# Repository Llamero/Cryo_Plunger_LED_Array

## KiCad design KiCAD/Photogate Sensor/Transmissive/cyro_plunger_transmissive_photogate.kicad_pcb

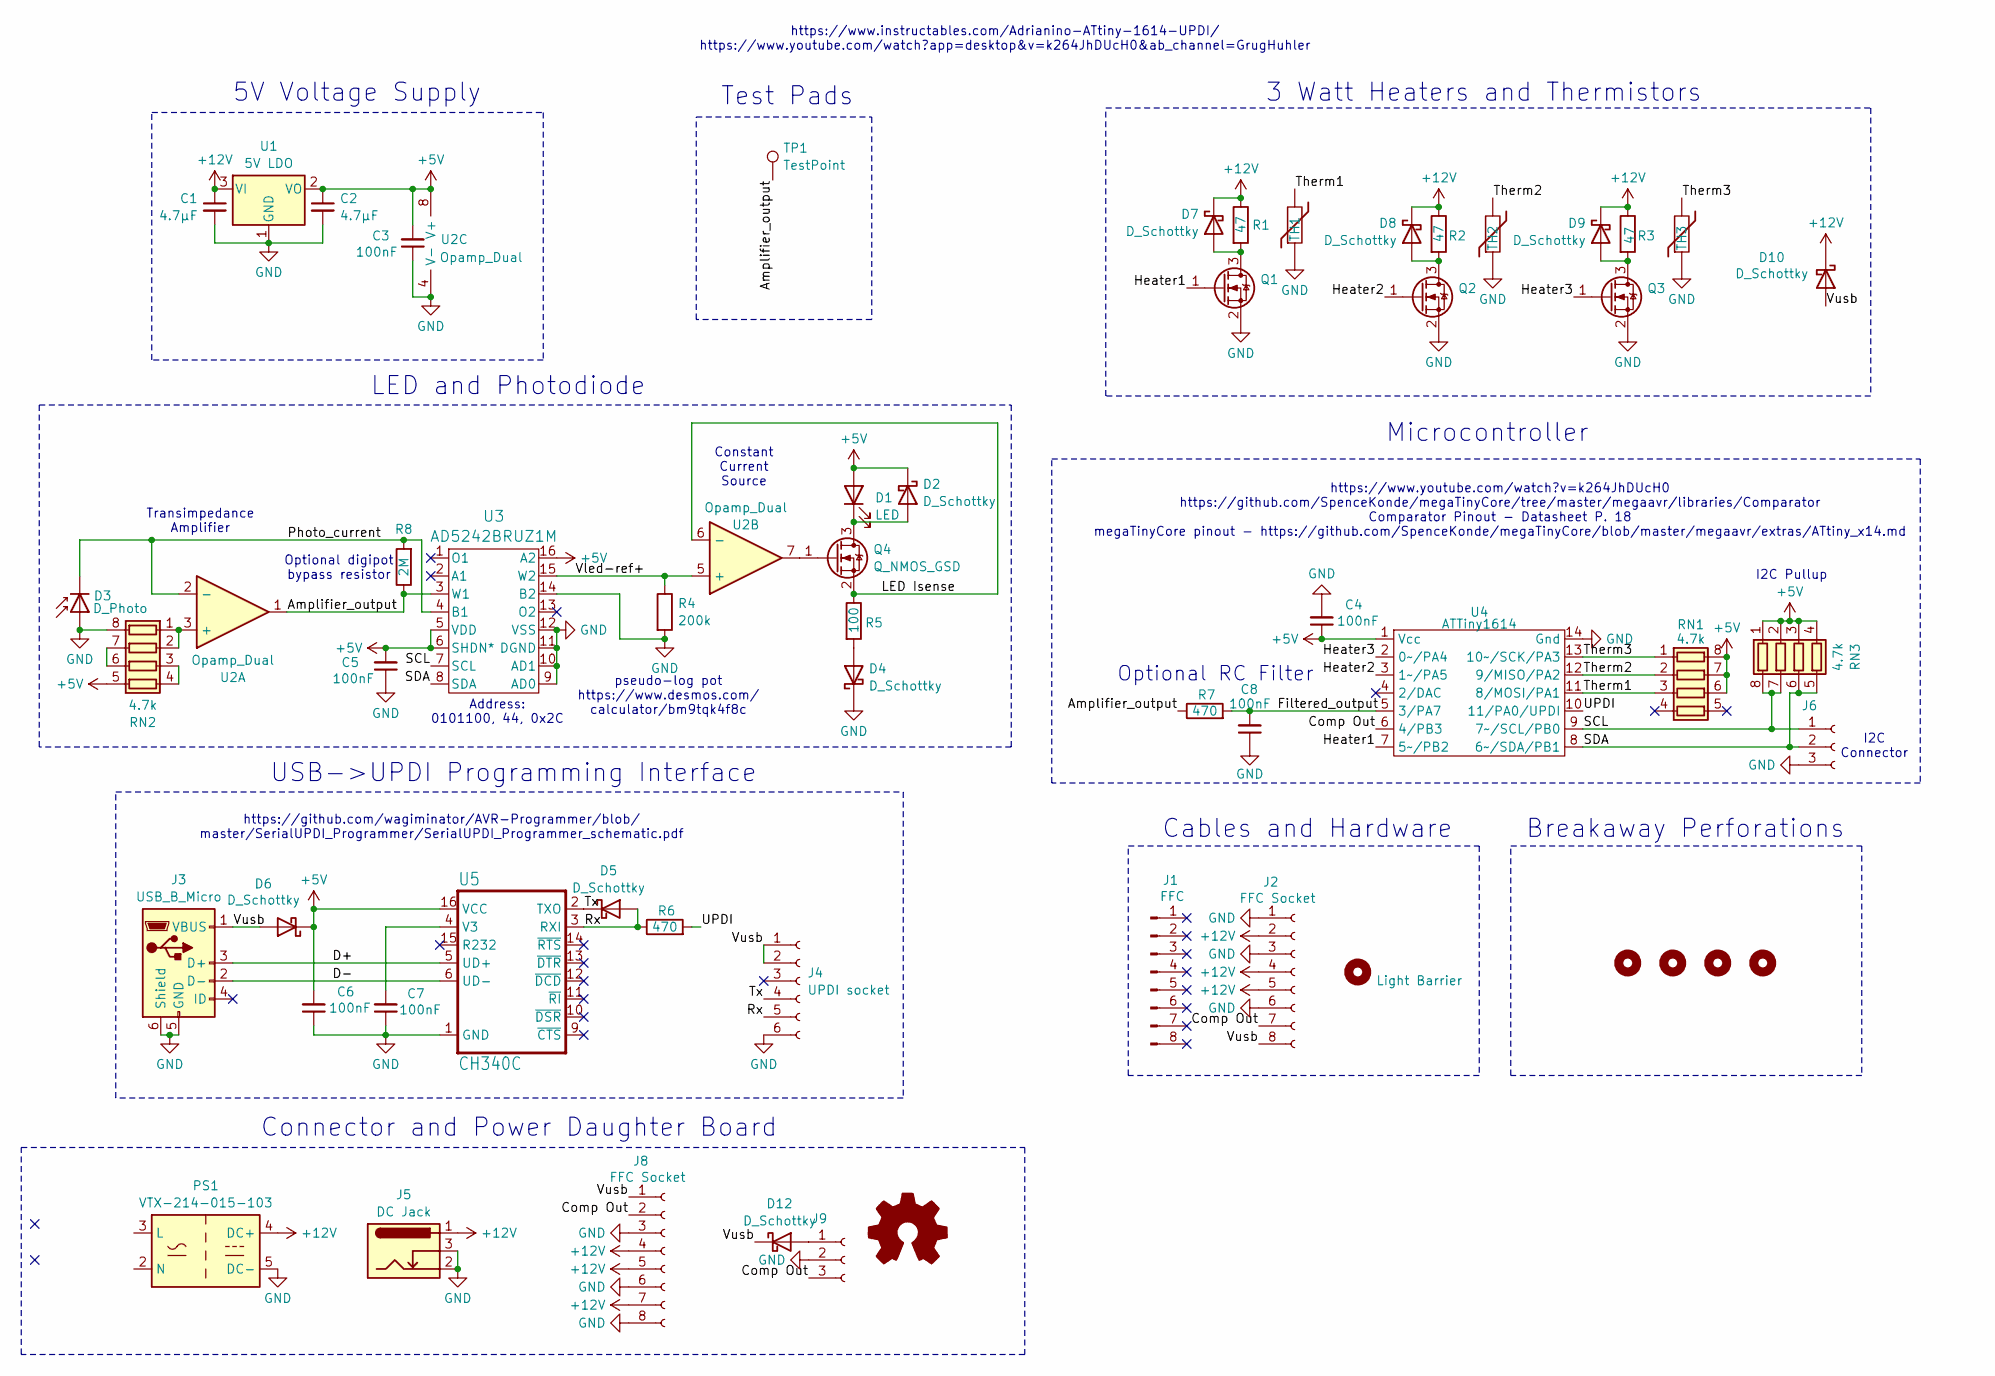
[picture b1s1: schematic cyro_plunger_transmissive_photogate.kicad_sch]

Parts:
C1, C2: 4.7µF; C_0805_2012Metric; Part GRT21BR61H475KE13L
C3, C4, C5, C6, C7, C8: 100nF; C_0805_2012Metric; Part MT21B104K500CT
D1: LED; Solder pads; Part SFH 4550
D2, D4, D5, D6, D7, D8, D9, D10, D12: D_Schottky; D_SOD-323; Part CUS10S30,H3F
D3: D_Photo; Solder pads; Part SFH 213 FA
H1: Light Barrier; Part B0CZ3GRKQH
H2, H3, H4, H5: mouse bite
J1: FFC; Part 0151670243
J2, J8: FFC Socket; AMPHENOL_SFW8S-2STE1LF; Part SFW8S-2STE1LF
J3: USB_B_Micro; CUI_UJ2-MIBH-G-SMT-TR; Part UJ2-MIBH-G-SMT-TR
J4: UPDI socket; PinSocket_1x06_P2.54mm_Vertical_SMD_Pin1Right; Part NPTC061KFXC-RC
J5: DC Jack; TENSILITY_54-00165; Part 54-00165
J6, J9: Conn_01x03_Socket; PinSocket_1x03_P2.54mm_Vertical_SMD_Pin1Right; Part NPPC031KFXC-RC
PS1: VTX-214-015-103
Q1, Q2, Q3, Q4: Q_NMOS_GSD; SOT-23-3; Part AS2312
R1, R2: 47; RES_SMF5_TYCO_TYC; Part SMW547RJT
R3: 47; RES_3550_TEC; Part 355047RJT
R4: 200k; R_0805_2012Metric; Part CPF-A-0805B200KE
R5: 100; R_1206_3216Metric; Part RP1206BRD07100RL
R6, R7: 470; R_0805_2012Metric; Part RP0805FRE07470RL
R8: 2M; R_0805_2012Metric; Part MCU0805MD2004BP500
RN1, RN2, RN3: 4.7k; R_Array_Convex_4x1206; Part YC324-FK-074K7L
SYM1: Logo_Open_Hardware_Small; polarity
TH1, TH2, TH3: Thermistor; R_0805_2012Metric; Part NCP21XM472J03RA
TP1: TestPoint; 1x Solder pads
U1: 5V LDO; SOT-223-3_TabPin2; Part LDL1117S50R
U2: Opamp_Dual; MSOP-8_3x3mm_P0.65mm; Part AD8607ARMZ-REEL
U3: AD5242BRUZ1M; Part AD5242BRUZ1M
U4: ATTiny1614; SOIC-14_3.9x8.7mm_P1.27mm; Part ATTINY1614-SSNR
U5: CH340C; SOP-16_3.9x9.9mm_P1.27mm; Part B0BK991VVV

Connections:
+5V: C2.1, C3.2, C4.1, C5.2, C6.2, D1.2 (A), D2.1 (K), D6.1 (K), RN1.6 (R3.2), RN1.7 (R2.2), RN1.8 (R1.2), RN2.5 (R4.2), RN3.1 (R1.1), RN3.2 (R2.1), RN3.3 (R3.1), RN3.4 (R4.1), U1.2 (VO), U2.8 (V+), U3.5 (VDD), U3.6 (SHDN*), U3.16 (A2), U4.1 (Vcc), U5.16 (VCC)
+12V: C1.1, D7.1 (K), D8.1 (K), D9.1 (K), D10.1 (K), J2.2, J2.4, J2.5, J5.1, J8.4, J8.5, J8.7, PS1.4 (DC+), R1.1, R2.1, R3.1, U1.3 (VI)
/Amplifier_output: R7.1, R8.1, TP1.1, U2.1, U3.3 (W1)
/Comp Out: J2.7, J8.2, J9.3, U4.6 (4/PB3)
/D+: J3.3 (D+), U5.5 (UD+)
/D-: J3.2 (D-), U5.6 (UD-)
/Filtered_output: C8.2, R7.2, U4.5 (3/PA7)
/Heater1: Q1.1 (G), U4.7 (5~/PB2)
/Heater2: Q2.1 (G), U4.3 (1~/PA5)
/Heater3: Q3.1 (G), U4.2 (0~/PA4)
/LED Isense: Q4.2 (S), R5.1, U2.6 (-)
/Photo_current: D3.1 (K), R8.2, U2.2 (-), U3.4 (B1)
/Rx: D5.2 (A), J4.5, R6.1, U5.3 (RXI)
/SCL: J6.1, RN3.7 (R2.2), RN3.8 (R1.2), U3.7 (SCL), U4.9 (7~/SCL/PB0)
/SDA: J6.2, RN3.5 (R4.2), RN3.6 (R3.2), U3.8 (SDA), U4.8 (6~/SDA/PB1)
/Therm1: RN1.3 (R3.1), TH1.2, U4.11 (8/MOSI/PA1)
/Therm2: RN1.2 (R2.1), TH2.2, U4.12 (9/MISO/PA2)
/Therm3: RN1.1 (R1.1), TH3.2, U4.13 (10~/SCK/PA3)
/Tx: D5.1 (K), J4.4, U5.2 (TXO)
/UPDI: R6.2, U4.10 (11/PA0/UPDI)
/Vled-ref+: R4.1, U2.5 (+), U3.15 (W2)
/Vusb: D6.2 (A), D10.2 (A), D12.1 (K), J2.8, J3.1 (VBUS), J4.1, J4.2, J8.1
GND: C1.2, C2.2, C3.1, C4.2, C5.1, C6.1, C7.1, C8.1, D3.2 (A), D4.1 (K), J2.1, J2.3, J2.6, J3.5 (GND), J3.6 (Shield), J4.6, J5.2, J5.3, J6.3, J8.3, J8.6, J8.8, J9.2, PS1.5 (DC-), Q1.2 (S), Q2.2 (S), Q3.2 (S), R4.2, RN2.8 (R1.2), TH1.1, TH2.1, TH3.1, U1.1 (GND), U2.4 (V-), U3.9 (AD0), U3.10 (AD1), U3.11 (DGND), U3.12 (VSS), U3.14 (B2), U4.14 (Gnd), U5.1 (GND)
unnamed: D1.1 (K), D2.2 (A), Q4.3 (D)
unnamed: D4.2 (A), R5.2
unnamed: D7.2 (A), Q1.3 (D), R1.2
unnamed: D8.2 (A), Q2.3 (D), R2.2
unnamed: D9.2 (A), Q3.3 (D), R3.2
unnamed: D12.2 (A), J9.1
unnamed: Q4.1 (G), U2.7
unnamed: RN2.1 (R1.1), RN2.2 (R2.1), U2.3 (+)
unnamed: RN2.6 (R3.2), RN2.7 (R2.2)
unnamed: RN2.3 (R3.1), RN2.4 (R4.1)
unnamed: C7.2, U5.4 (V3)

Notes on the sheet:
I2C Pullup
Optional RC Filter
https://www.youtube.com/watch?v=k264JhDUcH0 https://github.com/SpenceKonde/megaTinyCore/tree/master/megaavr/libraries/Comparator Comparator Pinout - Datasheet P. 18 megaTinyCore pinout - https://github.com/SpenceKonde/megaTinyCore/blob/master/megaavr/extras/ATtiny_x14.md
Breakaway Perforations
I2C Connector
Microcontroller
Constant Current Source
pseudo-log pot https://www.desmos.com/ calculator/bm9tqk4f8c
Connector and Power Daughter Board
Transimpedance Amplifier
https://github.com/wagiminator/AVR-Programmer/blob/ master/SerialUPDI_Programmer/SerialUPDI_Programmer_schematic.pdf
Optional digipot bypass resistor
5V Voltage Supply
Address: 0101100, 44, 0x2C
https://www.instructables.com/Adrianino-ATtiny-1614-UPDI/ https://www.youtube.com/watch?app=desktop&v=k264JhDUcH0&ab_channel=GrugHuhler
Cables and Hardware
LED and Photodiode
3 Watt Heaters and Thermistors
USB->UPDI Programming Interface
Test Pads

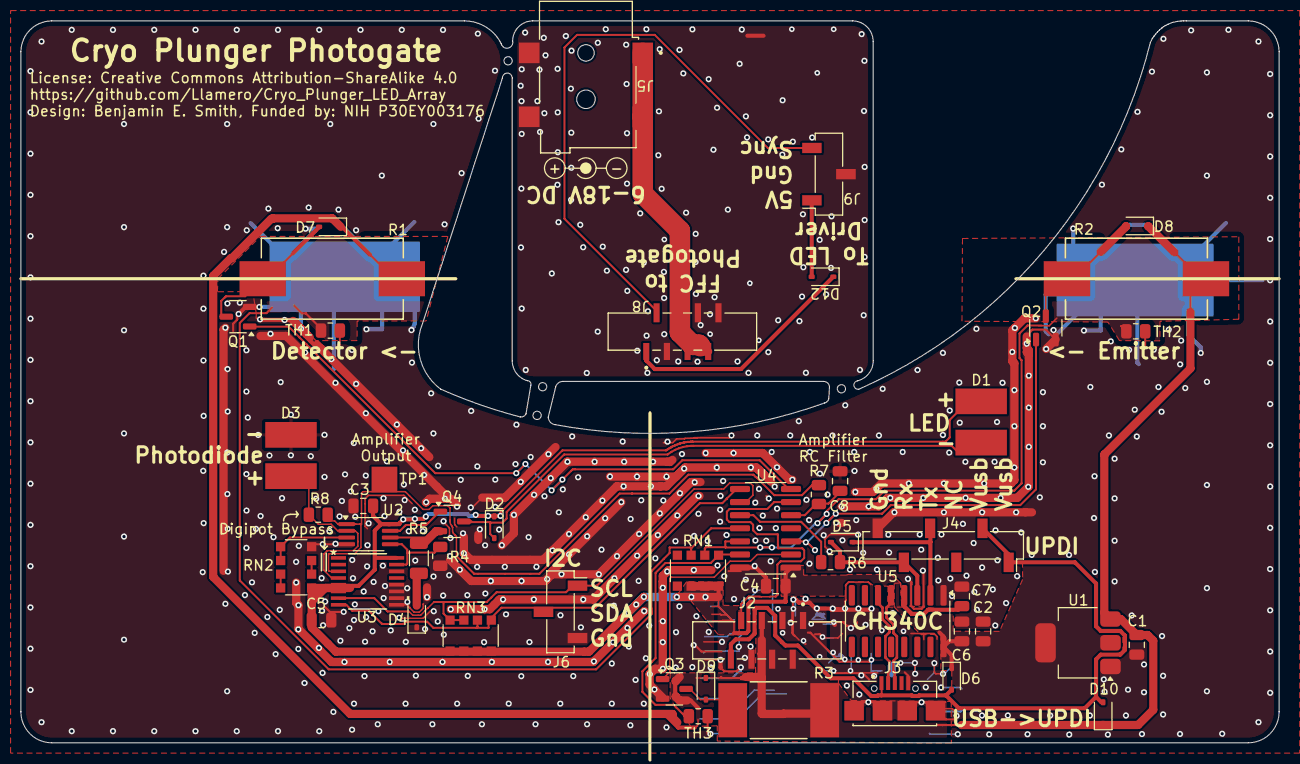
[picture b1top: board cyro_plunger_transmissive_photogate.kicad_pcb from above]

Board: 2 copper layers, 122.0 x 70.0 mm, 55 parts (0 on the bottom side), 34 nets.

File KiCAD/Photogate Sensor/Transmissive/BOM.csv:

Reference,Value,Datasheet,Footprint,Qty,Manufacturer,Part
"C1,C2",4.7µF,https://search.murata.co.jp/Ceramy/image/img/A01X/G101/ENG/G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,Capacitor_SMD:C_0805_2012Metric,2,Murata Electronics,GRT21BR61H475KE13L
"C3,C4,C5,C6,C7,C8",100nF,https://www.passivecomponent.com/wp-content/uploads/datashee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,Capacitor_SMD:C_0805_2012Metric,6,Walsin Technology Corporation,MT21B104K500CT
D1,LED,https://look.ams-osram.com/m/7d214b223a9adb85/original/SFH-4550.pdf,Custom:Solder pads,1,ams-OSRAM USA INC.,SFH 4550
"D2,D4,D6,D7,D8,D9,D10,D11,D12",D_Schottky,https://toshiba.semicon-storage.com/info/docget.jsp?did=1407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,Diode_SMD:D_SOD-323,9,Toshiba Semiconductor and Storage,"CUS10S30,H3F"
D3,D_Photo,https://look.ams-osram.com/m/3798e9afd3f63ea8/original/SFH-2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,Custom:Solder pads,1,ams-OSRAM USA INC.,SFH 213 FA
D5,D,https://www.mccsemi.com/pdf/Products/1N4148WX(SOD-323).pdf,Diode_SMD:D_SOD-323,1,MCC (Micro Commercial Components),1N4148WX-TP
H1,Light Barrier,uxcell 4Pcs Carbon Fiber Tube 4 x 6 x 200mm Pultruded Carbon Fiber Tubing for RC Airplane Kite Wing Tube Quadcopter Arm,,1,Amazon,B0CZ3GRKQH
J1,FFC,https://tools.molex.com/pdm_docs/ps/PS-15167-001-001.pdf,,1,Molex,151670243
"J2,J8",FFC Socket,https://cdn.amphenol-cs.com/media/wysiwyg/files/documentatio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,Custom:AMPHENOL_SFW8S-2STE1LF,2,Amphenol ICC (FCI),SFW8S-2STE1LF
"J3,J7",USB_B_Micro,https://www.cuidevices.com/product/resource/uj2-mibh-g-smt-tr.pdf,Custom:CUI_UJ2-MIBH-G-SMT-TR,2,Same Sky (Formerly CUI Devices),UJ2-MIBH-G-SMT-TR
J4,UPDI socket,https://mm.digikey.com/Volume0/opasdata/d220001/medias/docus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,Connector_PinSocket_2.54mm:PinSocket_1x06_P2.54mm_Vertical_SMD_Pin1Right,1,Sullins Connector Solutions,NPTC061KFXC-RC
J5,DC Jack,https://tensility.s3.us-west-2.amazonaws.com/uploads/pdffile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,Custom:TENSILITY_54-00165,1,Tensility International Corp,54-00165
"J6,J9",Conn_01x03_Socket,https://mm.digikey.com/Volume0/opasdata/d220001/medias/docus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,Connector_PinSocket_2.54mm:PinSocket_1x03_P2.54mm_Vertical_SMD_Pin1Right,2,Sullins Connector Solutions,NPPC031KFXC-RC
PS1,VTX-214-015-103,http://www.vigortronix.com/15WattSMPSPCBModuleAC-DC,,1,,
"Q1,Q2,Q3,Q4",Q_NMOS_GSD,https://mm.digikey.com/Volume0/opasdata/d220001/medias/docus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,Package_TO_SOT_SMD:SOT-23-3,4,ANBON SEMICONDUCTOR (INT'L) LIMITED,AS2312
"R1,R2",47,https://www.te.com/usa-en/product-6-1879233-5.datasheet.pdf,Custom:RES_SMF5_TYCO_TYC,2,TE Connectivity Passive Product,SMW547RJT
R3,47,https://www.te.com/usa-en/product-9-2176404-1.datasheet.pdf,Custom:RES_3550_TEC,1,TE Connectivity Passive Product,355047RJT
R4,200k,https://www.te.com/usa-en/product-6-2176238-8.datasheet.pdf,Resistor_SMD:R_0805_2012Metric,1,TE Connectivity Passive Product,CPF-A-0805B200KE
R5,100,https://www.yageo.com/upload/media/product/app/datasheet/rch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,Resistor_SMD:R_1206_3216Metric,1,YAGEO,RP1206BRD07100RL
"R6,R7",470,https://www.yageo.com/upload/media/product/app/datasheet/rch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,Resistor_SMD:R_0805_2012Metric,2,YAGEO,RP0805FRE07470RL
R8,2M,https://www.vishay.com/docs/28952/mcr0201at-mca1206at.pdf,Resistor_SMD:R_0805_2012Metric,1,Vishay Beyschlag/Draloric/BC Components,MCU0805MD2004BP500
"RN1,RN2,RN3",4.7k,https://www.yageo.com/upload/media/product/app/datasheet/rch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,Resistor_SMD:R_Array_Convex_4x1206,3,YAGEO,YC324-FK-074K7L
"TH1,TH2,TH3",Thermistor,https://www.murata.com/products/productdata/8796839149598/NT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,Resistor_SMD:R_0805_2012Metric,3,Murata Electronics,NCP21XM472J03RA
TP1,TestPoint,~,Custom:1x Solder pads,1,,
U1,5V LDO,https://www.st.com/content/ccc/resource/technical/document/d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,Package_TO_SOT_SMD:SOT-223-3_TabPin2,1,STMicroelectronics,LDL1117S50R
U2,Opamp_Dual,https://www.analog.com/media/en/technical-documentation/data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,Package_SO:MSOP-8_3x3mm_P0.65mm,1,Analog Devices Inc.,AD8607ARMZ-REEL
U3,AD5242BRUZ1M,https://www.analog.com/media/en/technical-documentation/data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,Custom:AD5242BRUZ1M,1,Analog Devices Inc.,AD5242BRUZ1M
U4,ATTiny1614,http://ww1.microchip.com/downloads/en/DeviceDoc/ATtiny1614-1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,Package_SO:SOIC-14_3.9x8.7mm_P1.27mm,1,Microchip Technology,ATTINY1614-SSNR
U5,CH340C,https://docs.sparkfun.com/SparkFun_RTK_Facet_mosaic/assets/c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,Package_SO:SOP-16_3.9x9.9mm_P1.27mm,1,Amazon,B0BK991VVV

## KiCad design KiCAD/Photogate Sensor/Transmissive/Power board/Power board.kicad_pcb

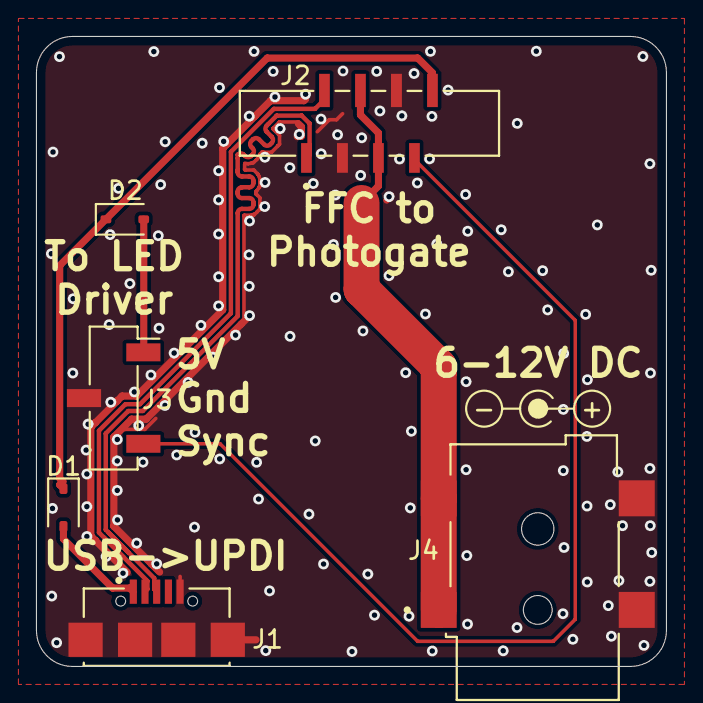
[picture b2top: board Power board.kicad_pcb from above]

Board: 2 copper layers, 35.0 x 35.0 mm, 7 parts (0 on the bottom side), 8 nets.

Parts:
D1, D2: D_Schottky; D_SOD-323
J1: USB_B_Micro; CUI_UJ2-MIBH-G-SMT-TR
J2: FFC Socket; AMPHENOL_SFW8S-2STE1LF
J3: Conn_01x03_Socket; PinSocket_1x03_P2.54mm_Vertical_SMD_Pin1Right
J4: DC Jack; TENSILITY_54-00165
SYM1: Logo_Open_Hardware_Small; polarity

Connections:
+12V: J2.4, J2.5, J4.1
/Comp Out: J2.7, J3.3
/D+: J1.3 (D+), J2.1
/D-: J1.2 (D-), J2.2
/Vusb: D1.1 (K), D2.1 (K), J2.8
GND: J1.5 (GND), J1.6 (Shield), J2.3, J2.6, J3.2, J4.2, J4.3
unnamed: D1.2 (A), J1.1 (VBUS)
unnamed: D2.2 (A), J3.1

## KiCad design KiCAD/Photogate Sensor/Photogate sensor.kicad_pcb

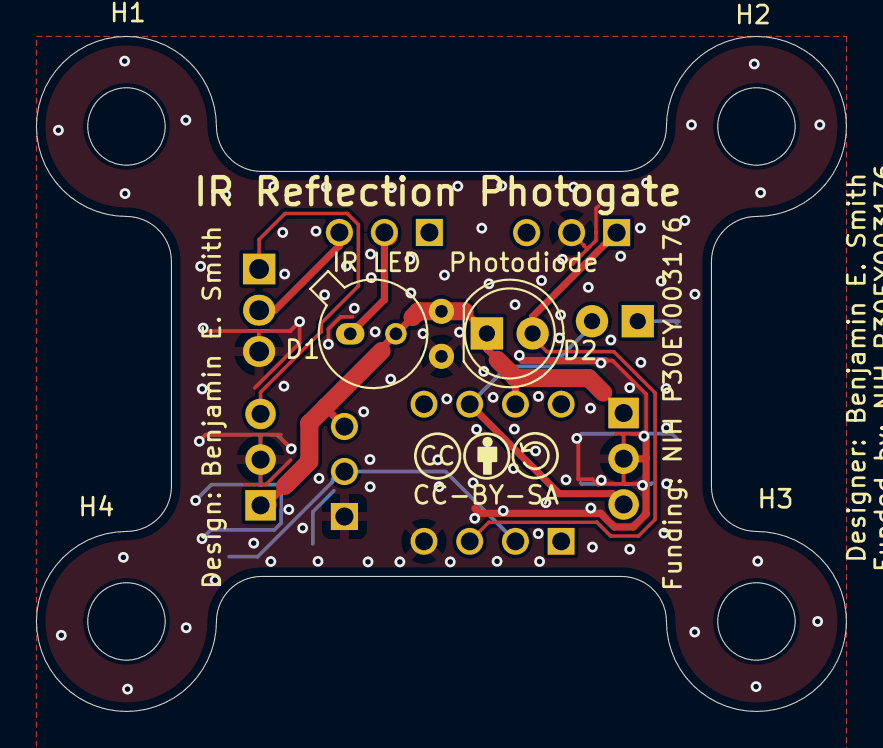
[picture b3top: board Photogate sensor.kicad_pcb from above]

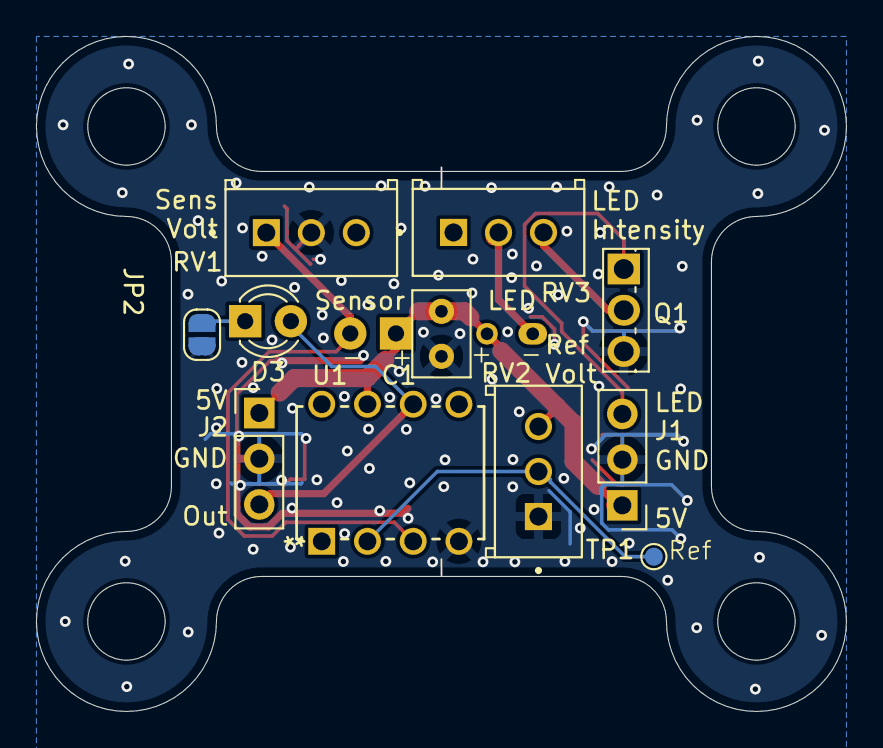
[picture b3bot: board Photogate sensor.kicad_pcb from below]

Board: 2 copper layers, 45.0 x 37.5 mm, 18 parts (11 on the bottom side), 9 nets.

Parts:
C1: 100nF; C_Rect_L4.6mm_W3.0mm_P2.50mm_MKS02_FKP02
D1: LED; TO-46-2 - nIR
D2: D_Photo; LED_D5.0mm - nIR
D3: LED; LED_D3.0mm
H1, H2, H3, H4: MountingHole; MountingHole_4.3mm_M4
J1, J2: Conn_01x03_Pin; PinHeader_1x03_P2.54mm_Vertical
JP2: Jumper_2_Open; SolderJumper-2_P1.3mm_Open_RoundedPad1.0x1.5mm
Q1: Q_NMOS_GDS; TO-251-3_Vertical
RV1, RV2, RV3: 50k; TRIM_PV36W503C01B00
SYM1: Logo_Open_Hardware_Small; CC-BY-SA Symbol
TP1: TestPoint; TestPoint_Pad_D1.0mm
U1: MCP6541; PDIP8_300MC_MCH

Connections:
/5V: C1.1, D1.2 (A), D2.1 (K), J1.1, J2.1, RV2.3, U1.7 (VDD)
/Comp+: D2.2 (A), RV1.1, U1.3 (VIN+)
/LED control: J1.3, Q1.1 (G)
/Trigger: D3.2 (A), J2.3, U1.6 (OUT)
GND: C1.2, J1.2, J2.2, JP2.1 (A), Q1.3 (S), RV1.2, RV2.1, U1.4 (VSS)
unnamed: D1.1 (K), RV3.2
unnamed: D3.1 (K), JP2.2 (B)
unnamed: Q1.2 (D), RV3.3
unnamed: RV2.2, TP1.1, U1.2 (VIN-)

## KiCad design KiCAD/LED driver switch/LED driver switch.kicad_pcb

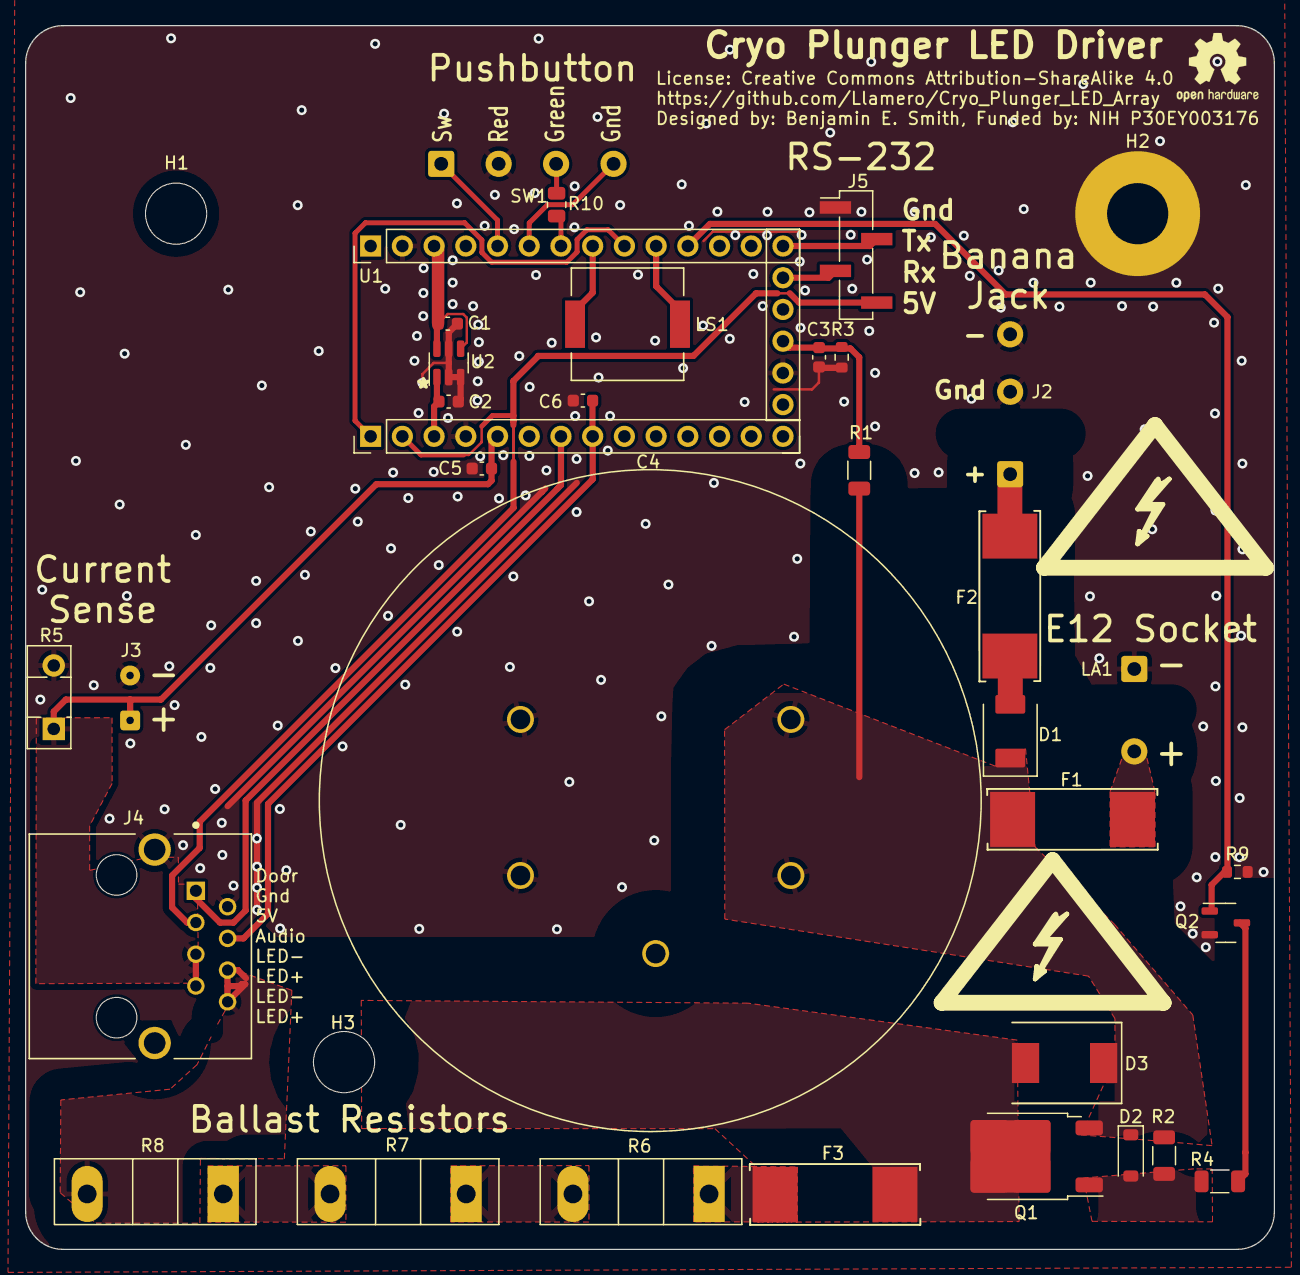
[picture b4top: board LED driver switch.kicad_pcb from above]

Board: 2 copper layers, 100.0 x 98.0 mm, 40 parts (1 on the bottom side), 29 nets.

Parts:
C1: 2.2µF; C_0603_1608Metric
C2, C3, C5, C6: 1nF; C_0603_1608Metric
C4: 3mF; ALF20G302KP400
D1: D; P26_DO-214AA_SMB
D2: 15V Zener; D_SOD-123
D3: TVS; SMDJSeries_LTF
F1, F2, F3: Fuse; FUSE_OMF250_SCH
H1, H3: Standoff; 8-32 Isolated Hole
H2: Standoff; 8-32 Standoff
J2: 3x Banana Jack; SolderWire-0.5sqmm_1x03_P4.6mm_D0.9mm_OD2.1mm - HV Slot
J3: Conn_Coaxial; SolderWire-0.1sqmm_1x02_P3.6mm_D0.4mm_OD1mm
J4: 8P8C_Shielded; BEL_SS71800-019F - HV Slot
J5: Conn_01x04_Pin; PinHeader_1x04_P2.54mm_Vertical_SMD_Pin1Left
LA1: E12 Socket; SolderWire-0.5sqmm_1x02_P4.6mm_D0.9mm_OD2.1mm - HV Slot
LS1: Speaker_Crystal; XDCR_SMT-0940-T-3V-R
Q1: PMOS; TO-252-2 - HV
Q2: TN2124; SOT-23-3 - HV Slot
R1: 1M; R_1206_3216 - HV slot
R2: 100k; R_1206_3216Metric
R3, R9: 20k; R_0603_1608Metric
R4: 100k; R_1206_3216 - HV slot
R5: 1; TO-126-2_Vertical
R6, R7, R8: 10; TO-247-2_Vertical
R10: 180; R_0805_2012Metric
SW1: SW_Push_LED; SolderWire-0.5sqmm_1x04_P4.6mm_D0.9mm_OD2.1mm
SYM1: SYM_Flash_Small; Symbol_HighVoltage
SYM2, SYM2#2: SYM_Flash_Small; Symbol_Highvoltage_Type2_CopperTop_Small
SYM3: Logo_Open_Hardware_Small; OSHW-Logo2_7.3x6mm_SilkScreen
U1: Itsy_Bitsy_32u4; Itsy Bitsy 32u4
U2: 4.096V; SOT-23-6

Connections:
+5V: J4.3, J5.4, U1.2 (5V)
/0-200V: C4.1, C4.2, D1.1 (K), D2.1 (K), D3.1 (K), F1.2, Q1.3 (S), R1.1, R2.1
/Aref: C2.1, U1.3 (ARef), U2.1 (OUT)
/Audio out: C6.1, J4.4, U1.8 (21_A3)
/Door safety interlock: J4.1, U1.7 (20_A2)
/Green_LED: SW1.4, U1.28 (~11)
/Isense: C5.1, J3.1 (In), J4.5, J4.7, R5.1, U1.5 (18_A0)
/LED+: J4.6, J4.8, R8.2
/LED_trigger: Q2.1 (G), R9.1, U1.23 (~3_SCL)
/Power supply+: F2.1, J2.1
/Pushbutton: SW1.1, U1.29 (12_A11)
/RS-232 Rx: J5.3, U1.19 (4_A6)
/RS-232 Tx: J5.2, U1.20 (0_RX)
/Red_LED: R10.1, U1.27 (~10_A10)
/Vbus: C1.1, U1.31 (VBus), U2.4 (SHDN), U2.6 (Vdd)
/Vsense: C3.1, R1.2, R3.1, U1.17 (8_A8)
/reset: U1.1 (Reset), U1.25 (7)
GND: C1.2, C2.2, C3.2, C4.3, C4.4, C5.2, C6.2, H2.1, J2.2, J2.3, J3.2 (Ext), J4.2, J4.SH, J5.1, LA1.1 (R1.1), Q2.2 (S), R3.2, R5.2, R9.2, SW1.2, U1.4 (GND), U1.16 (Gnd), U1.32 (Gnd), U2.2 (GND), U2.3 (GND), U2.5 (GND)
unnamed: D1.2 (A), F2.2
unnamed: D2.2 (A), Q1.1 (G), R2.2, R4.1
unnamed: D3.2 (A), F3.2, Q1.2 (D)
unnamed: F3.1, R6.1
unnamed: F1.1, LA1.2 (R2.1)
unnamed: Q2.3 (D), R4.2
unnamed: R6.2, R7.1
unnamed: R7.2, R8.1
unnamed: R10.2, SW1.3
unnamed: LS1.2, U1.24 (~5)
unnamed: LS1.1, U1.26 (~9_A9)

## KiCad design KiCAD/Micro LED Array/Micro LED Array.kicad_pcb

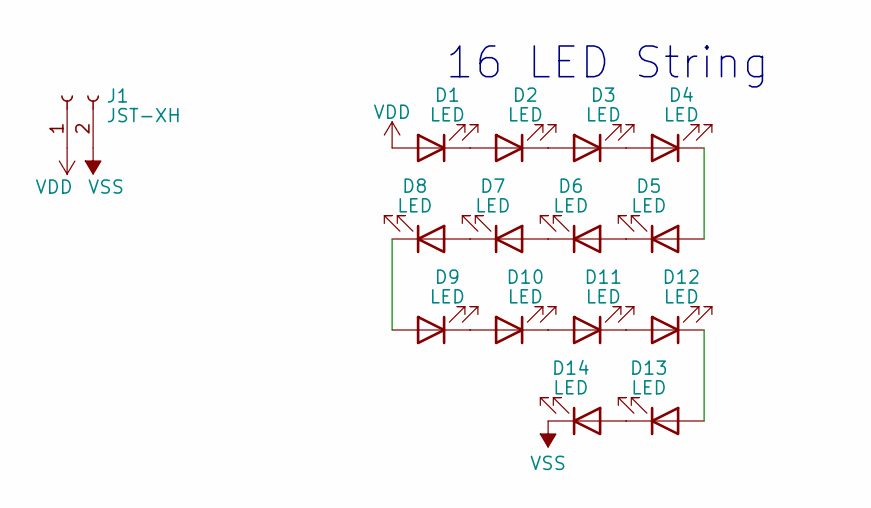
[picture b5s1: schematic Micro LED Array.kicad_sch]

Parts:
D1, D2, D3, D4, D5, D6, D7, D8, D9, D10, D11, D12, D13, D14: LED; LED_XLAMP_XE-G_CRW; Part XEGARY-H0-0000-000-000000K2001
J1: JST-XH; SolderWire-0.5sqmm_1x02_P10.5mm_D0.9mm_OD2.1mm; Part B2B-XH-A

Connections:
unnamed: D1.1 (K), D2.2 (A)
unnamed: D2.1 (K), D3.2 (A)
unnamed: D3.1 (K), D4.2 (A)
unnamed: D4.1 (K), D5.2 (A)
unnamed: D5.1 (K), D6.2 (A)
unnamed: D6.1 (K), D7.2 (A)
unnamed: D7.1 (K), D8.2 (A)
unnamed: D8.1 (K), D9.2 (A)
unnamed: D9.1 (K), D10.2 (A)
unnamed: D10.1 (K), D11.2 (A)
unnamed: D11.1 (K), D12.2 (A)
unnamed: D12.1 (K), D13.2 (A)
unnamed: D13.1 (K), D14.2 (A)
VDD: D1.2 (A), J1.1
VSS: D14.1 (K), J1.2

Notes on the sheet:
16 LED String

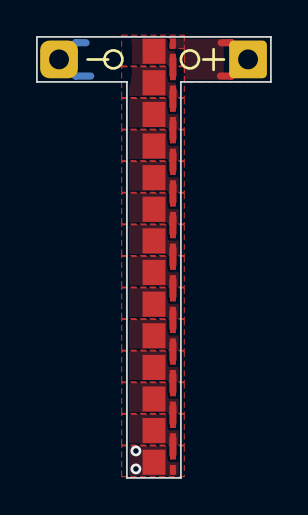
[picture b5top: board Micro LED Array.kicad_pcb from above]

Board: 2 copper layers, 13.0 x 24.5 mm, 15 parts (0 on the bottom side), 15 nets.

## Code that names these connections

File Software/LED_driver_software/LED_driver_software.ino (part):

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#define LED_PWM 1
#define LED_FLASH_INTERVAL 500
#define off 0
#define red 10 //Device armed for LED trigger
#define flashing_red 11 //Cooling down LED and discharging cap
#define green 20 //Driver in standby
#define flashing_green 21 //Driver in standby due to error condition
#define yellow 40 //Calibrated waiting for press to arm trigger
#define flashing_yellow 41 //Calibrating

//System parameters
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const struct inputPinsStruct{
  uint8_t rx = 4;
  uint8_t photogate = 22; //Pin 21 was damaged, so bypassed to pin 22
  uint8_t pushbutton = 12;
  uint8_t pedal = 20;
} in;
const uint8_t in_pins[sizeof(in)] = {in.rx, in.photogate, in.pushbutton, in.pedal};

const struct outputPinsStruct{
  uint8_t led[2] = {10, 11};
  uint8_t speaker[2] = {5, 9};
  uint8_t led_trigger = 3;
  uint8_t tx = 0;
} out;
const uint8_t out_pins[sizeof(out)] = {out.led[0], out.led[1], out.speaker[0], out.speaker[1], out.led_trigger, out.tx};

const struct analogPinsStruct{
  uint8_t vsense = 8;
  uint8_t isense = 18;
} ana;
const uint8_t ana_pins[sizeof(ana)] = {ana.vsense, ana.isense};

constexpr static struct stateStruct{
  uint8_t standby = 0;
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const uint8_t TIMING_PULSE_DURATION = 50;
const uint16_t FLASH_INTERVAL = 500;
const float VREF = 4.2; //ADC Vref
const float VFACTOR = 0.01960784313; //Voltage divider on Vsense
const uint32_t MAX_DURATION = 200000; //Maximum duration of LED pulse- prevents LEDs from overheating
uint8_t status_index;
bool flash; //Tracks whether led is on or off when flashing
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  for(i=0; i<sizeof(ana_pins); i++) analogRead(ana_pins[i]);
  digitalWriteFast(out.led_trigger, LOW); //Ensure LED output is disabled
  pinMode(LED_BUILTIN, OUTPUT);
  pinMode(ana.isense+1, OUTPUT);
  //configrue adc
  //analogReference(EXTERNAL); //External ADC is causing noise issues

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
void failSafe(){
  uint32_t cur_time = driver_timer;
  pinMode(out.led_trigger, OUTPUT);
  digitalWriteFast(out.led_trigger, LOW);
  ps.connect();
}
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
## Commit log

2024-08-27 56 LED strip
2024-08-27 56 strip 2
2024-09-12 Add bodge pads to diagnose and bypass LEDs
2024-09-14 Add fuses, RS232, Vref, Vsense, Isense
2024-09-16 Add safety interlocks
2024-09-19 Current setup
2024-09-20 Initial draft
2024-09-20 revise border
2024-09-28 Working PCB draft
2024-09-28 Controller moved - DRC pass
2024-09-30 test commit
2024-09-30 standoffs and enclosure added
2024-10-01 Widen wire spacing
2024-10-01 Add pulldown to gate, move LED pin to PWM
2024-10-01 Move cap and standoff, fix cap polarity, add jumper 0V to GND
2024-10-02 Move high voltage away from board edge - build enclosure model
2024-10-08 Add high voltage slots
2024-10-08 Add label
2024-10-09 Ordered version
2024-10-19 Add HV slots for mosfet
2024-10-29 Upload working RS232 r/w code
2024-10-31 Added button led timers and more PS commands
2024-10-31 get and set voltage working
2024-10-31 Fixed adc by turning off external vref
2024-11-01 Untested add pulse struct and audio tones
2024-11-02 untested calibration function added
2024-11-02 Add comments to LED states
2024-11-04 Add error handler - untested
2024-11-05 Autocalibration and error handlers working
2024-11-05 Remove serial wait
2024-11-07 Add pulse function, door check
2024-11-08 Update PCB to reflect current design
2024-11-14 Improve com timing and update driver current limits
2024-12-22 Add photogate design
2024-12-24 Add status LED, improve traces
2025-01-16 Add pedal feature
2025-01-24 Update trimpot values
2025-05-13 Starting on transmissive photogate
2025-05-13 More revisions
2025-05-14 Finish draft of schematic, started on board
2025-05-15 Analog and digital circuits mostly connected
2025-05-15 More connections
2025-05-15 More path optimization
2025-05-16 Add RC filter and I2C breakout - passes DRC
2025-05-16 Add digipot bypass - upgrade to moisture resistance when possible
2025-05-16 A license info to board
2025-05-16 Add plunger reference line
2025-05-17 Thermally isolated heaters
2025-05-20 connection board wired and skew matched
2025-05-20 Skew matched and impedance approx. 90 ohm on photogate board
2025-05-20 USB skew matched and impedance set to approx. 90 ohms
2025-05-20 Add skew on power board D+ to offset skew on photogate board
2025-05-20 Place Gnds closer to data lines on FFC
2025-05-20 More ground optimizations
2025-05-21 Panelize boards - improve 12V thermal pad
2025-05-21 Remove separate power board
2025-05-31 replace silicon updi diode with schottky
2025-05-31 Add pullup to reset line
2025-06-02 heater control test with autotune PWM
2025-06-10 Better heater control, photodiode autocalibration
2025-06-10 reduce bias gain autothreshold
2025-06-12 Interrupt sync working
2025-06-12 Working photogate code!
2025-06-12 Add comments
2025-06-14 Woeking draft with LED driver integrated
2025-06-18 Remove second USB connector
2025-06-23 Calibrate threshold to grid

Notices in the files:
KiCAD/LED driver switch/LED driver switch.kicad_pcb:
License: Creative Commons Attribution-ShareAlike 4.0
